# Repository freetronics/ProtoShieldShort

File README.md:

Freetronics ProtoShieldShort
==============================
Copyright 2011 Freetronics Pty Ltd  
Freetronics site:  <www.freetronics.com>  
Freetronics email: <info@freetronics.com>  

A special short prototyping shield for the Arduino, designed to be able
to clear the RJ45 jack on an Ethernet Shield or Freetronics EtherTen.

Note that this design is intended for simple fabrication and assembly,
and does not have many of the features of other prototyping shields
such as the "ProtoShield" (also available from Freetronics) such as
general-purpose LEDs.

Features:

 * Pads for reset button connected to Arduino reset pin.
 * Parts overlay on both the top and the bottom so you can see what you
   are connecting without having to keep turning the board over.

More information is available at:

  http://www.freetronics.com/protoshield-short

The "docs" folder within this repository includes a handy copy of the
schematic in PDF format and image(s) of the pcb.

INSTALLATION
------------
The design is saved as an EAGLE project. EAGLE PCB design software is
available from www.cadsoftusa.com free for non-commercial use. To use
this project download it and place the directory containing these files
into the "eagle" directory on your computer. Then open EAGLE and
navigate to Projects -> eagle -> ProtoShieldShort.

DISTRIBUTION
------------
The specific terms of distribution of this project are governed by the
license referenced below.

LICENSE
-------
Licensed under the TAPR Open Hardware License (www.tapr.org/OHL).
The "license" folder within this repository also contains a copy of
this license in plain text format.

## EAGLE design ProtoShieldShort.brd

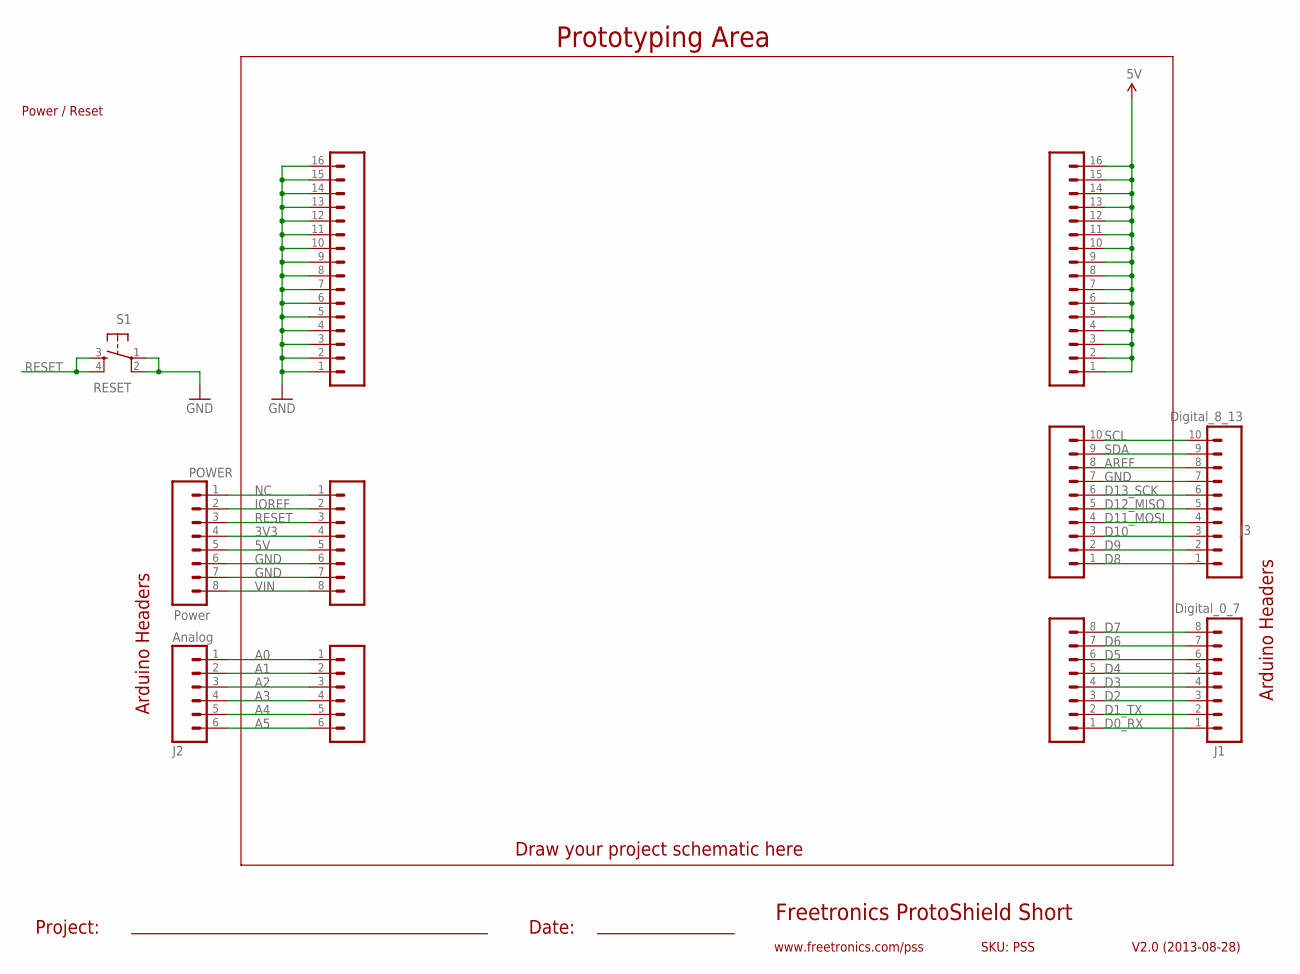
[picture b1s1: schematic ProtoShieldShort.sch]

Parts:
J1: Digital_0_7; 1X08
J2: Analog; 1X06
J3: Digital_8_13; 1X10
PADS_5V: M16PTH; 1X16
PADS_GND: M16PTH; 1X16
POWER: Power; 1X08
S1: RESET; TACTILE-PTH
SL1: Digital_0_7; 1X08
SL2: Analog; 1X06
SL3: Digital_8_13; 1X10
SLP: Power; 1X08

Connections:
3V3: POWER.4, SLP.4
5V: PADS_5V.1, PADS_5V.2, PADS_5V.3, PADS_5V.4, PADS_5V.5, PADS_5V.6, PADS_5V.7, PADS_5V.8, PADS_5V.9, PADS_5V.10, PADS_5V.11, PADS_5V.12, PADS_5V.13, PADS_5V.14, PADS_5V.15, PADS_5V.16, POWER.5, SLP.5
A0: J2.1, SL2.1
A1: J2.2, SL2.2
A2: J2.3, SL2.3
A3: J2.4, SL2.4
A4: J2.5, SL2.5
A5: J2.6, SL2.6
AREF: J3.8, SL3.8
D0_RX: J1.1, SL1.1
D1_TX: J1.2, SL1.2
D2: J1.3, SL1.3
D3: J1.4, SL1.4
D4: J1.5, SL1.5
D5: J1.6, SL1.6
D6: J1.7, SL1.7
D7: J1.8, SL1.8
D8: J3.1, SL3.1
D9: J3.2, SL3.2
D10: J3.3, SL3.3
D11_MOSI: J3.4, SL3.4
D12_MISO: J3.5, SL3.5
D13_SCK: J3.6, SL3.6
GND: J3.7, PADS_GND.1, PADS_GND.2, PADS_GND.3, PADS_GND.4, PADS_GND.5, PADS_GND.6, PADS_GND.7, PADS_GND.8, PADS_GND.9, PADS_GND.10, PADS_GND.11, PADS_GND.12, PADS_GND.13, PADS_GND.14, PADS_GND.15, PADS_GND.16, POWER.6, POWER.7, S1.1, S1.2, SL3.7, SLP.6, SLP.7
IOREF: POWER.2, SLP.2
NC: POWER.1, SLP.1
RESET: POWER.3, S1.3, S1.4, SLP.3
SCL: J3.10, SL3.10
SDA: J3.9, SL3.9
VIN: POWER.8, SLP.8

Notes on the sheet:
Freetronics ProtoShield Short
V2.0 (2013-08-28)
www.freetronics.com/pss
SKU: PSS
Prototyping Area
Arduino Headers
Power / Reset
Project:
Date:
Draw your project schematic here

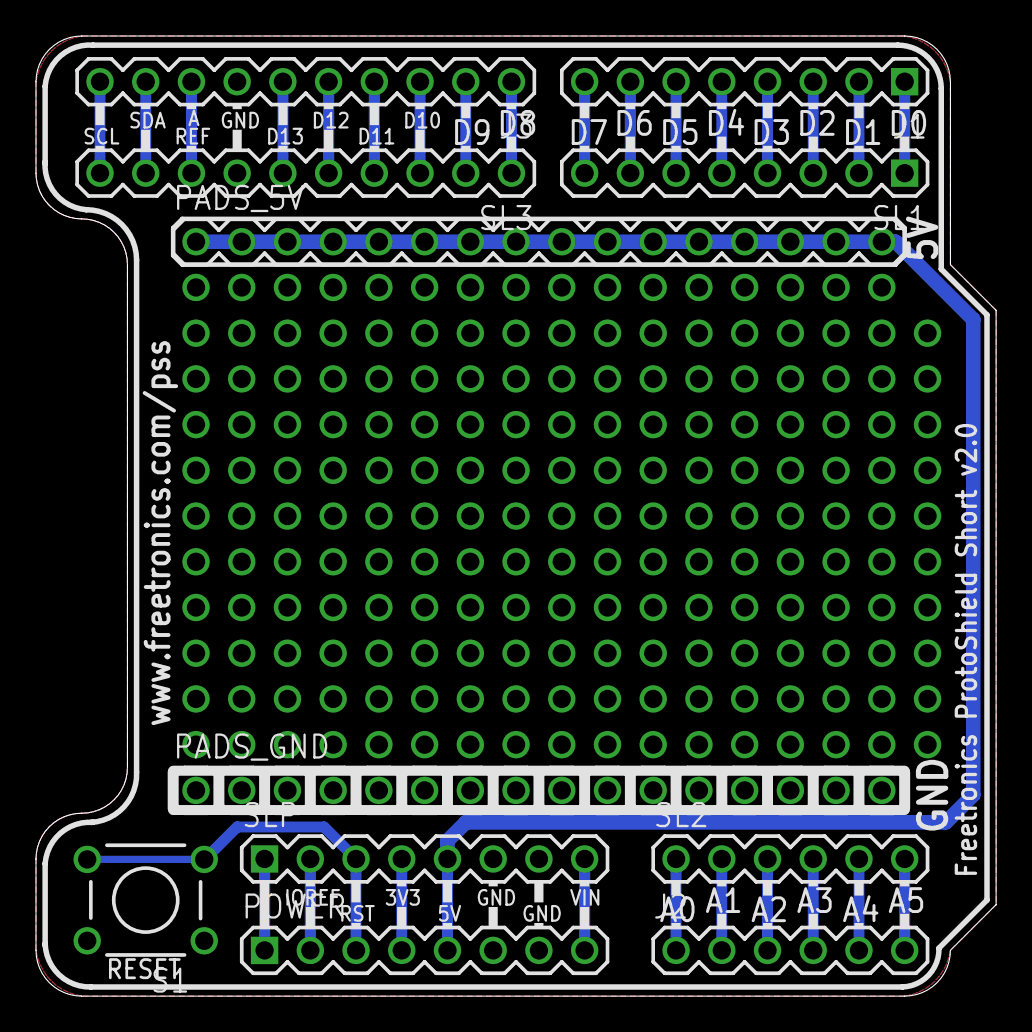
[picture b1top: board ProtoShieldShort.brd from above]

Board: 2 copper layers, 53.3 x 53.3 mm, 11 parts (0 on the bottom side), 30 nets.

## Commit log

2011-04-28 Added initial project files
2013-08-28 Updates to R3 headers and v2.0 release

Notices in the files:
ProtoShieldShort.brd:
(c) 2013 Freetronics Pty Ltd
